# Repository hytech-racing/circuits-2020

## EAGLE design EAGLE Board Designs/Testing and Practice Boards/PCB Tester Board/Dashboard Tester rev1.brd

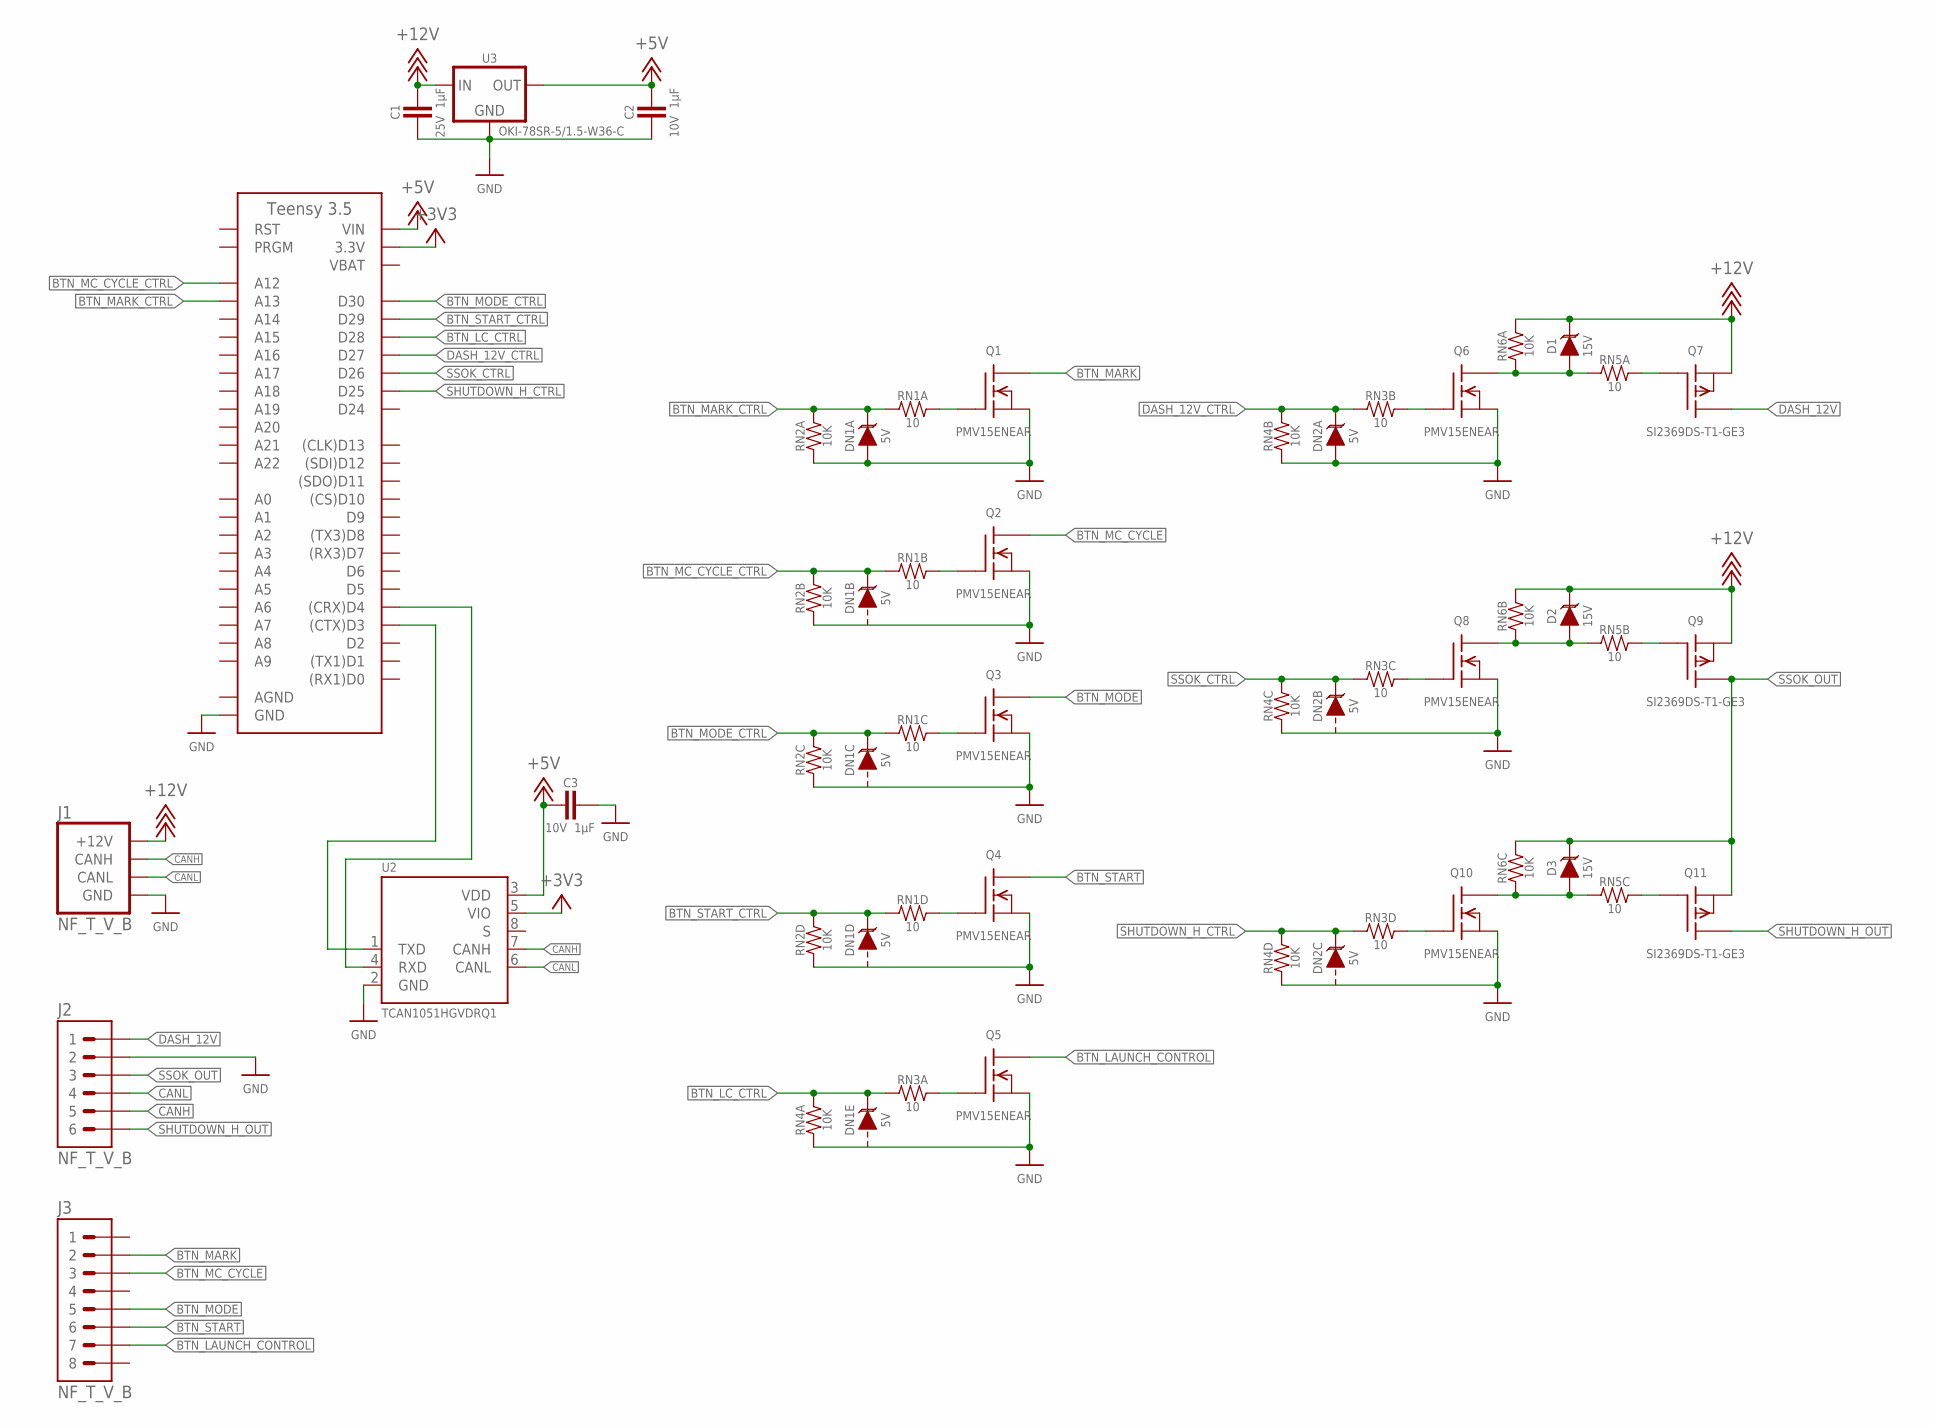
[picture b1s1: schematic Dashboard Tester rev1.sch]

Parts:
C1: CAPACITOR_0603_25V_1UF; 0603-CAP
C2, C3: CAPACITOR_0603_10V_1UF; 0603-CAP
D1, D2, D3: TVS_15V; SOT-23
DN1, DN2: TVS_ARRAY_5V; SOT363
J1: CONNECTOR-CAN_NF_T_V_BLACK; MOLEX_NANOFIT_PTH_04
J2: CONNECTOR-6_NF_T_V_BLACK; MOLEX_NANOFIT_PTH_06
J3: CONNECTOR-8_NF_T_V_BLACK; MOLEX_NANOFIT_PTH_08
Q1, Q2, Q3, Q4, Q5, Q6, Q8, Q10: TRANSISTOR_N_MOS_PMV15ENEA; SOT-23
Q7, Q9, Q11: TRANSISTOR_P_MOS_SOT23_SI2369DS-T1-GE3; SOT-23
RN1, RN3, RN5: RESISTOR_NETWORK_4_10; 1206-RES
RN2, RN4, RN6: RESISTOR_NETWORK_4_10K; 1206-RES
U1: TEENSY_3.5; TEENSY_LONG_EXT
U2: CAN_TRANSCIEVER_TCAN1051HQV-Q1; SOIC-08
U3: VOLTAGE_REGULATOR_OKI-78SR_5V; OKI-78SR

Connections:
+3V3: U1.3V3 (3.3V), U1.3V3@2 (3.3V), U1.3V3@3 (3.3V), U2.5 (VIO)
+5V: C2.1, C3.2, U1.VIN, U2.3 (VDD), U3.3 (OUT)
+12V: C1.1, D1.3 (C), D2.3 (C), J1.1 (+12V), Q7.2 (S), Q9.2 (S), RN6.7 (2), RN6.8 (2), U3.1 (IN)
AGND: U1.AGND/GND (AGND)
BTN_LAUNCH_CONTROL: J3.7, Q5.3 (D)
BTN_LC_CTRL: DN1.6 (C), RN3.1, RN4.8 (2), U1.D28
BTN_MARK: J3.2, Q1.3 (D)
BTN_MARK_CTRL: DN1.1 (C), RN1.1, RN2.8 (2), U1.D32 (A13)
BTN_MC_CYCLE: J3.3, Q2.3 (D)
BTN_MC_CYCLE_CTRL: DN1.3 (C), RN1.2 (1), RN2.7 (2), U1.D31 (A12)
BTN_MODE: J3.5, Q3.3 (D)
BTN_MODE_CTRL: DN1.4 (C), RN1.3 (1), RN2.6 (2), U1.D30
BTN_START: J3.6, Q4.3 (D)
BTN_START_CTRL: DN1.5 (C), RN1.4 (1), RN2.5 (2), U1.D29
CANH: J1.4 (CANH), J2.5, U2.7 (CANH)
CANL: J1.3 (CANL), J2.4, U2.6 (CANL)
DASH_12V: J2.1, Q7.3 (D)
DASH_12V_CTRL: DN2.1 (C), RN3.2 (1), RN4.7 (2), U1.D27
GND: C1.2, C2.2, C3.1, DN1.2 (A), DN2.2 (A), J1.2 (GND), J2.2, Q1.2 (S), Q2.2 (S), Q3.2 (S), Q4.2 (S), Q5.2 (S), Q6.2 (S), Q8.2 (S), Q10.2 (S), RN2.1, RN2.2 (1), RN2.3 (1), RN2.4 (1), RN4.1, RN4.2 (1), RN4.3 (1), RN4.4 (1), U1.GND, U1.GND@2 (GND), U1.GND@3 (GND), U2.2 (GND), U3.2 (GND)
unnamed: Q1.1 (G), RN1.8 (2)
unnamed: U1.D4 ((CRX)D4), U2.4 (RXD)
unnamed: Q6.1 (G), RN3.7 (2)
unnamed: Q2.1 (G), RN1.7 (2)
unnamed: Q3.1 (G), RN1.6 (2)
unnamed: Q4.1 (G), RN1.5 (2)
unnamed: Q5.1 (G), RN3.8 (2)
unnamed: Q8.1 (G), RN3.6 (2)
unnamed: Q9.1 (G), RN5.7 (2)
unnamed: D2.1 (A), Q8.3 (D), RN5.2 (1), RN6.2 (1)
unnamed: Q7.1 (G), RN5.8 (2)
unnamed: Q10.1 (G), RN3.5 (2)
unnamed: D1.1 (A), Q6.3 (D), RN5.1, RN6.1
unnamed: U1.D3 ((CTX)D3), U2.1 (TXD)
unnamed: Q11.1 (G), RN5.6 (2)
unnamed: D3.1 (A), Q10.3 (D), RN5.3 (1), RN6.3 (1)
SHUTDOWN_H_CTRL: DN2.4 (C), RN3.4 (1), RN4.5 (2), U1.D25
SHUTDOWN_H_OUT: J2.6, Q11.3 (D)
SSOK_CTRL: DN2.3 (C), RN3.3 (1), RN4.6 (2), U1.D26
SSOK_OUT: D3.3 (C), J2.3, Q9.3 (D), Q11.2 (S), RN6.6 (2)
VBAT: U1.VBAT

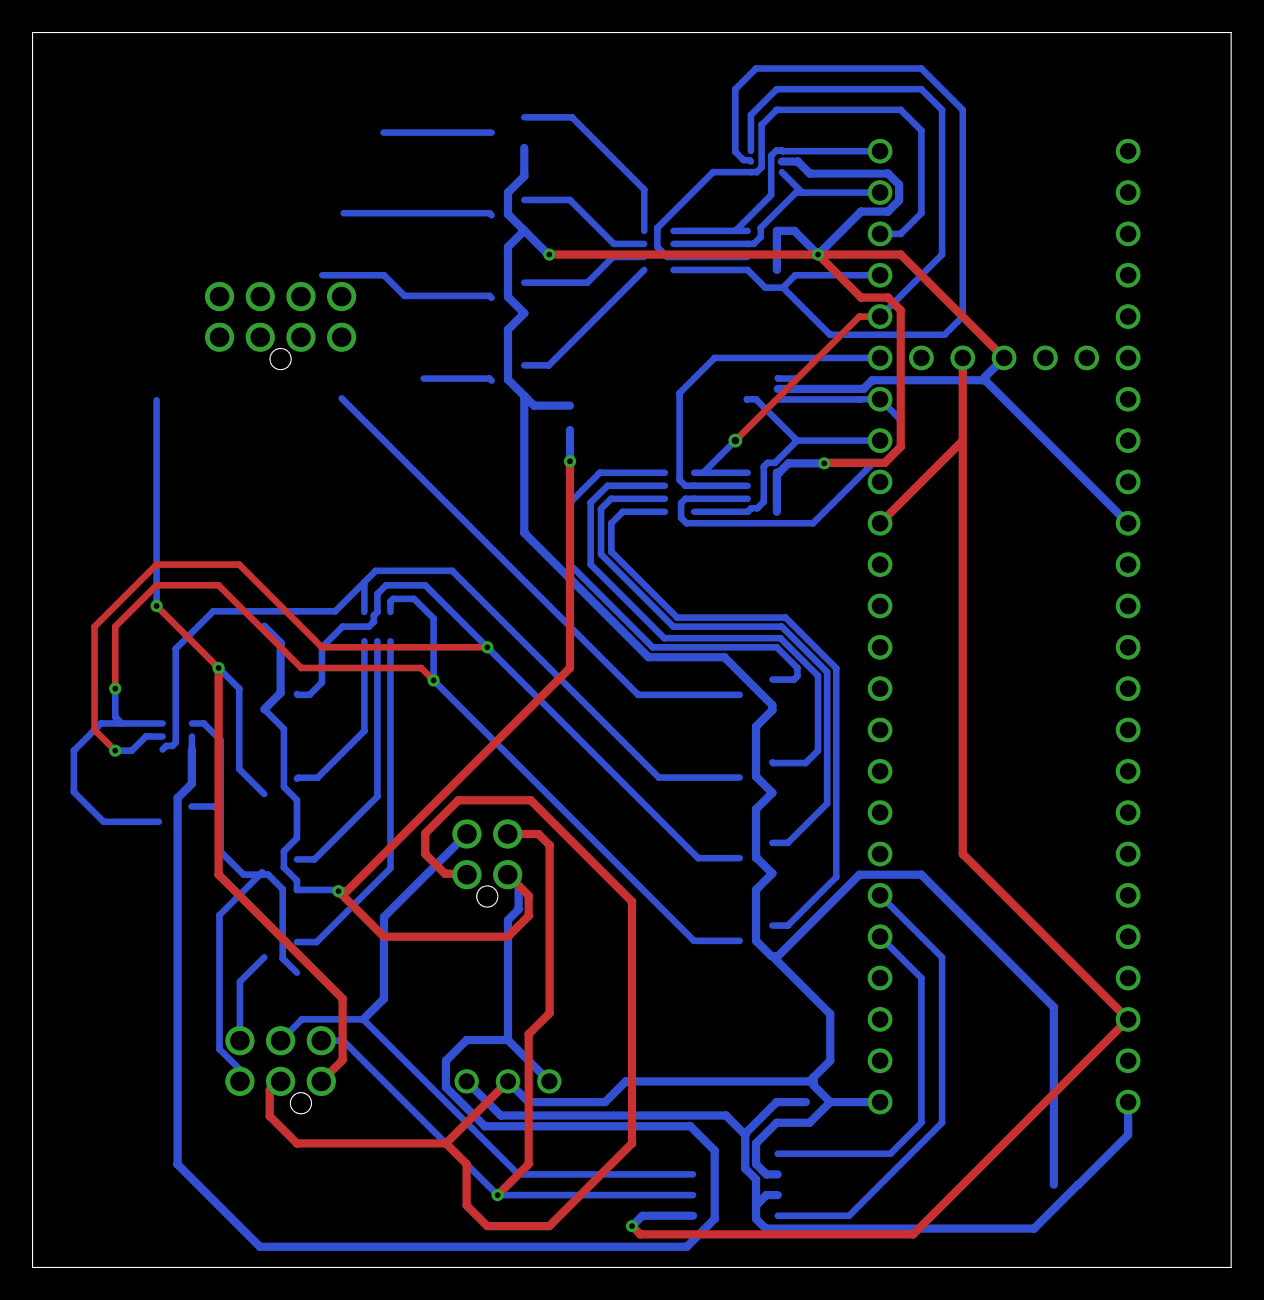
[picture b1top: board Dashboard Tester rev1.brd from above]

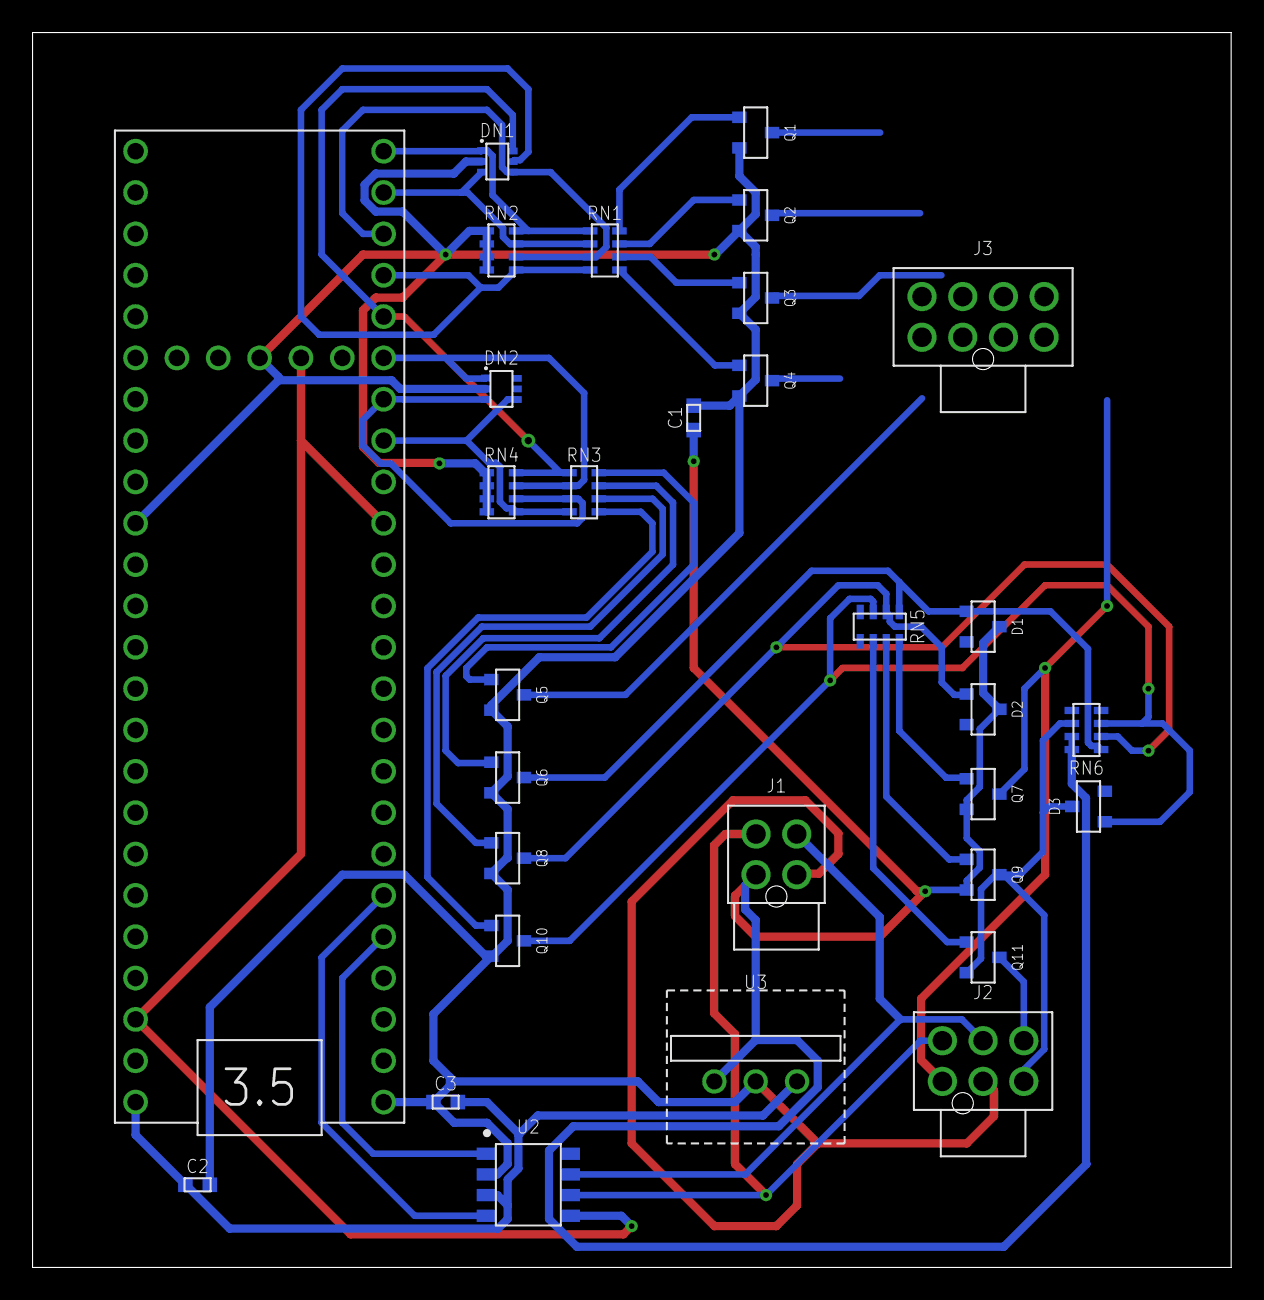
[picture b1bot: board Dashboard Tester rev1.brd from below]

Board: 2 copper layers, 73.6 x 75.9 mm, 31 parts (31 on the bottom side), 38 nets.

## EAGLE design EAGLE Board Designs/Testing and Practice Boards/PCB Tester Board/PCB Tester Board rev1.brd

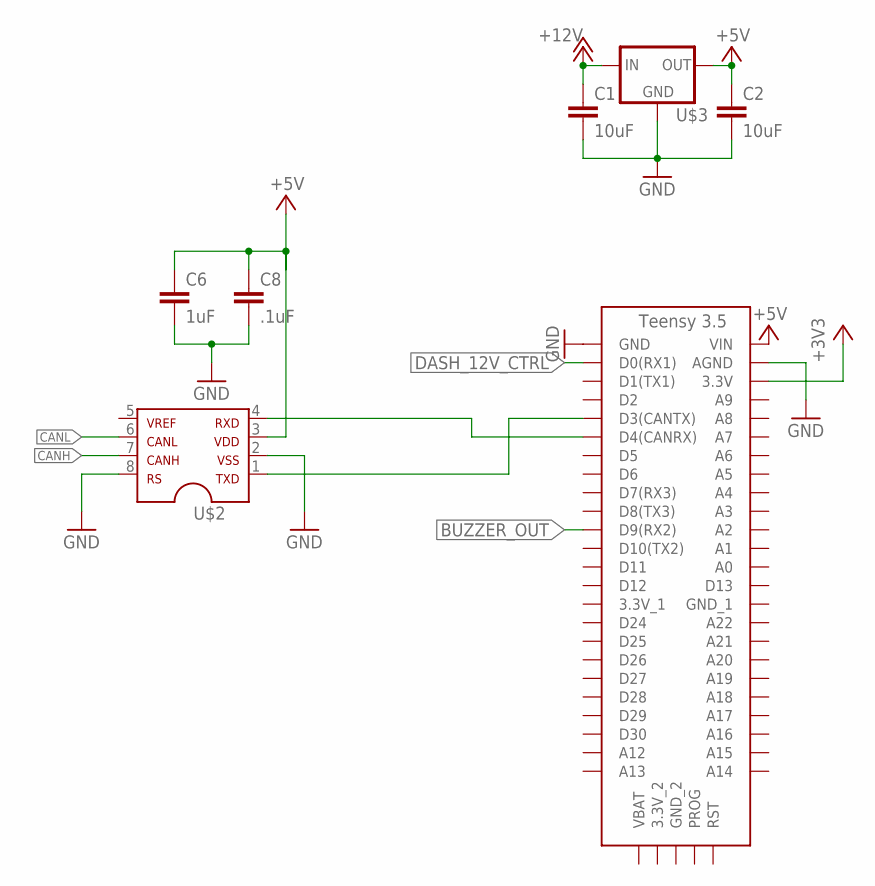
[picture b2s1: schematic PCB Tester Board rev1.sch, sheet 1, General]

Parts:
C1, C2: 10uF; 0603-CAP
C6: 1uF; 0603-CAP
C8: .1uF; 0603-CAP
U$2: MCP2551; SOIC-08
U$3: OKI-78SR-5; OKI-78SR
U$10: TEENSY_3.5_EXT

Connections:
+3V3: U$10.3.3V; also elsewhere on the board
+5V: C2.1, C6.1, C8.1, U$2.3, U$3.3 (OUT), U$10.VIN; also elsewhere on the board
+12V: C1.1, U$3.1 (IN); also elsewhere on the board
BUZZER_OUT: U$10.D9(RX2); also elsewhere on the board
CANH: U$2.7; also elsewhere on the board
CANL: U$2.6; also elsewhere on the board
DASH_12V_CTRL: U$10.D0(RX1); also elsewhere on the board
GND: C1.2, C2.2, C6.2, C8.2, U$2.2, U$2.8, U$3.2 (GND), U$10.AGND, U$10.GND; also elsewhere on the board
unnamed: U$2.1, U$10.D3(CANTX)
unnamed: U$2.4, U$10.D4(CANRX)

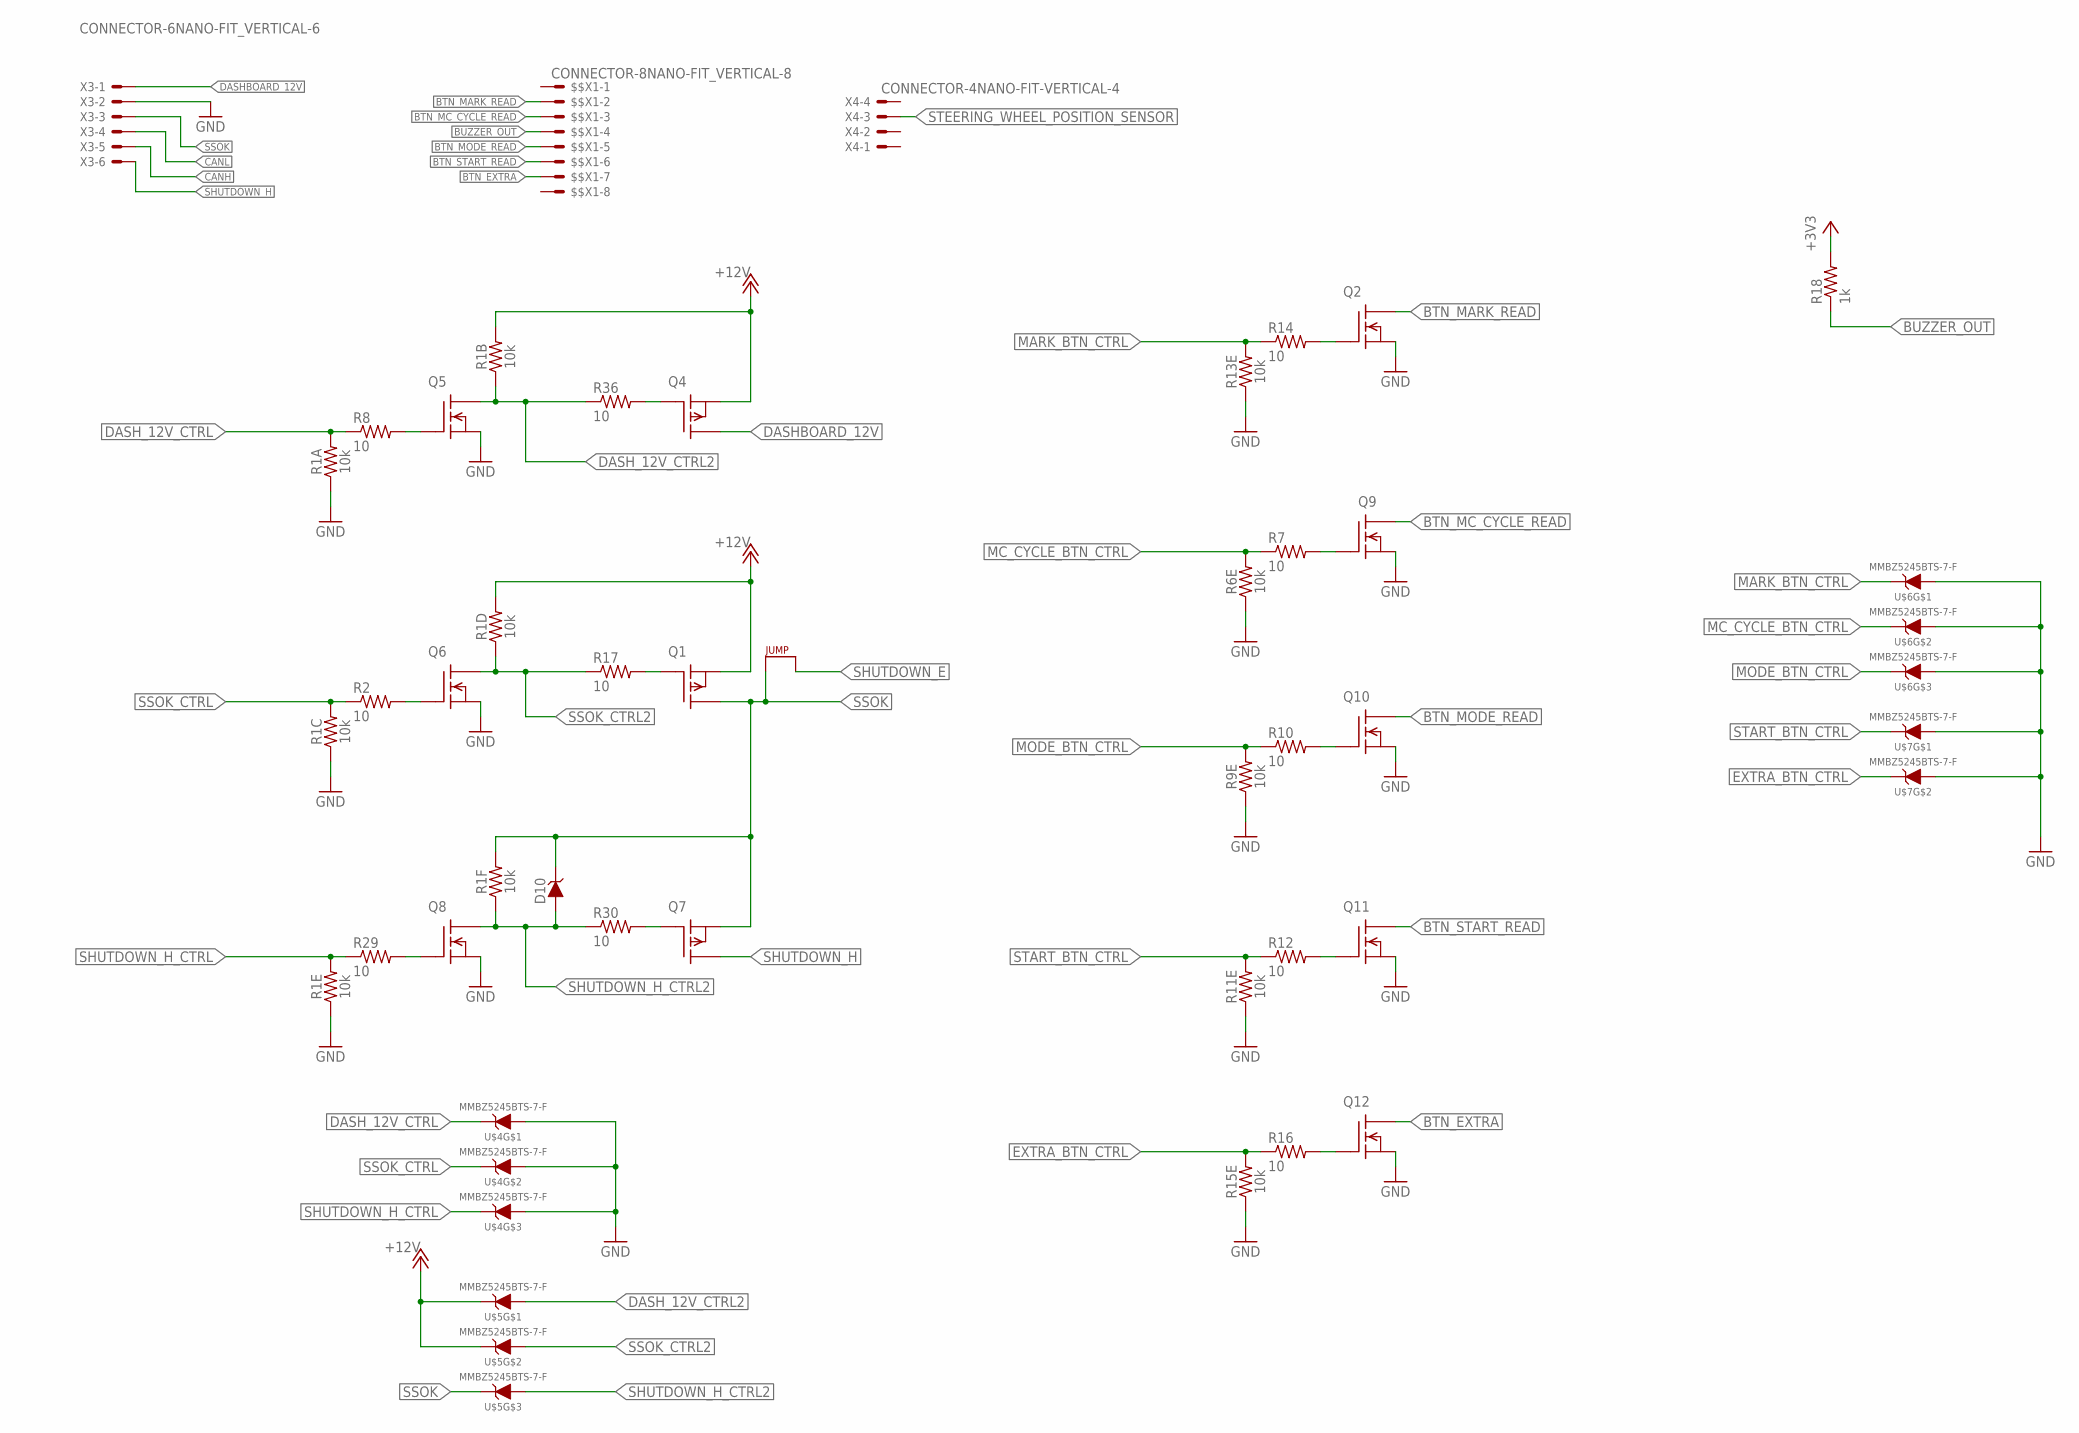
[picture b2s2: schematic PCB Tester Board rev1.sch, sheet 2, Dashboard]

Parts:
$$X1: CONNECTOR-8NANO-FIT_VERTICAL-8; NANO-FIT_VERTICAL-8
D10: DIODE_ZENER; SOT23
J4: JUMPER.1; 1X02
Q1, Q4, Q7: P-CHANNEL_MOSFET_DMP3099L-7; SOT23
Q2, Q5, Q6, Q8, Q9, Q10, Q11, Q12: DMG3406LSOT; SOT23
R1, R6, R9, R11, R13, R15: 10k; YAG_YC248-M
R2, R7, R8, R10, R12, R14, R16, R17, R29, R30, R36: 10; 0603-RES
R18: 1k; 0603-RES
U$4, U$5, U$6, U$7: MMBZ5245BTS-7-F; SOT363
X3: CONNECTOR-6NANO-FIT_VERTICAL-6; NANO-FIT_VERTICAL-6
X4: CONNECTOR-4NANO-FIT-VERTICAL-4; NANO-FIT_VERTICAL-4

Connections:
+3V3: R18.2; also elsewhere on the board
+12V: Q1.2 (S), Q4.2 (S), R1.13 (2), R1.15 (2), U$5.P$4 (C), U$5.P$5 (C); also elsewhere on the board
BTN_EXTRA: $$X1.P$7, Q12.3 (D)
BTN_MARK_READ: $$X1.P$2, Q2.3 (D)
BTN_MC_CYCLE_READ: $$X1.P$3, Q9.3 (D)
BTN_MODE_READ: $$X1.P$5, Q10.3 (D)
BTN_START_READ: $$X1.P$6, Q11.3 (D)
BUZZER_OUT: $$X1.P$4, R18.1; also elsewhere on the board
CANH: X3.P$5; also elsewhere on the board
CANL: X3.P$4; also elsewhere on the board
DASHBOARD_12V: Q4.3 (D), X3.P$1
DASH_12V_CTRL: R1.16 (2), R8.1, U$4.P$4 (C); also elsewhere on the board
DASH_12V_CTRL2: Q5.3 (D), R1.2 (1), R36.1, U$5.P$1 (A)
EXTRA_BTN_CTRL: R15.12 (2), R16.1, U$7.P$5 (C)
GND: Q2.2 (S), Q5.2 (S), Q6.2 (S), Q8.2 (S), Q9.2 (S), Q10.2 (S), Q11.2 (S), Q12.2 (S), R1.1, R1.3 (1), R1.5 (1), R6.5 (1), R9.5 (1), R11.5 (1), R13.5 (1), R15.5 (1), U$4.P$1 (A), U$4.P$2 (A), U$4.P$3 (A), U$6.P$1 (A), U$6.P$2 (A), U$6.P$3 (A), U$7.P$1 (A), U$7.P$2 (A), X3.P$2; also elsewhere on the board
MARK_BTN_CTRL: R13.12 (2), R14.1, U$6.P$4 (C)
MC_CYCLE_BTN_CTRL: R6.12 (2), R7.1, U$6.P$5 (C)
MODE_BTN_CTRL: R9.12 (2), R10.1, U$6.P$6 (C)
unnamed: Q9.1 (G), R7.2
unnamed: Q10.1 (G), R10.2
unnamed: Q11.1 (G), R12.2
unnamed: Q5.1 (G), R8.2
unnamed: Q12.1 (G), R16.2
unnamed: Q2.1 (G), R14.2
unnamed: Q6.1 (G), R2.2
unnamed: Q1.1 (G), R17.2
unnamed: Q8.1 (G), R29.2
unnamed: Q7.1 (G), R30.2
unnamed: Q4.1 (G), R36.2
SHUTDOWN_E: J4.2; also elsewhere on the board
SHUTDOWN_H: Q7.3 (D), X3.P$6
SHUTDOWN_H_CTRL: R1.12 (2), R29.1, U$4.P$6 (C)
SHUTDOWN_H_CTRL2: D10.1 (A), Q8.3 (D), R1.6 (1), R30.1, U$5.P$3 (A)
SSOK: D10.3 (C), J4.1, Q1.3 (D), Q7.2 (S), R1.11 (2), U$5.P$6 (C), X3.P$3
SSOK_CTRL: R1.14 (2), R2.1, U$4.P$5 (C)
SSOK_CTRL2: Q6.3 (D), R1.4 (1), R17.1, U$5.P$2 (A)
START_BTN_CTRL: R11.12 (2), R12.1, U$7.P$4 (C)
STEERING_WHEEL_POSITION_SENSOR: X4.P$3

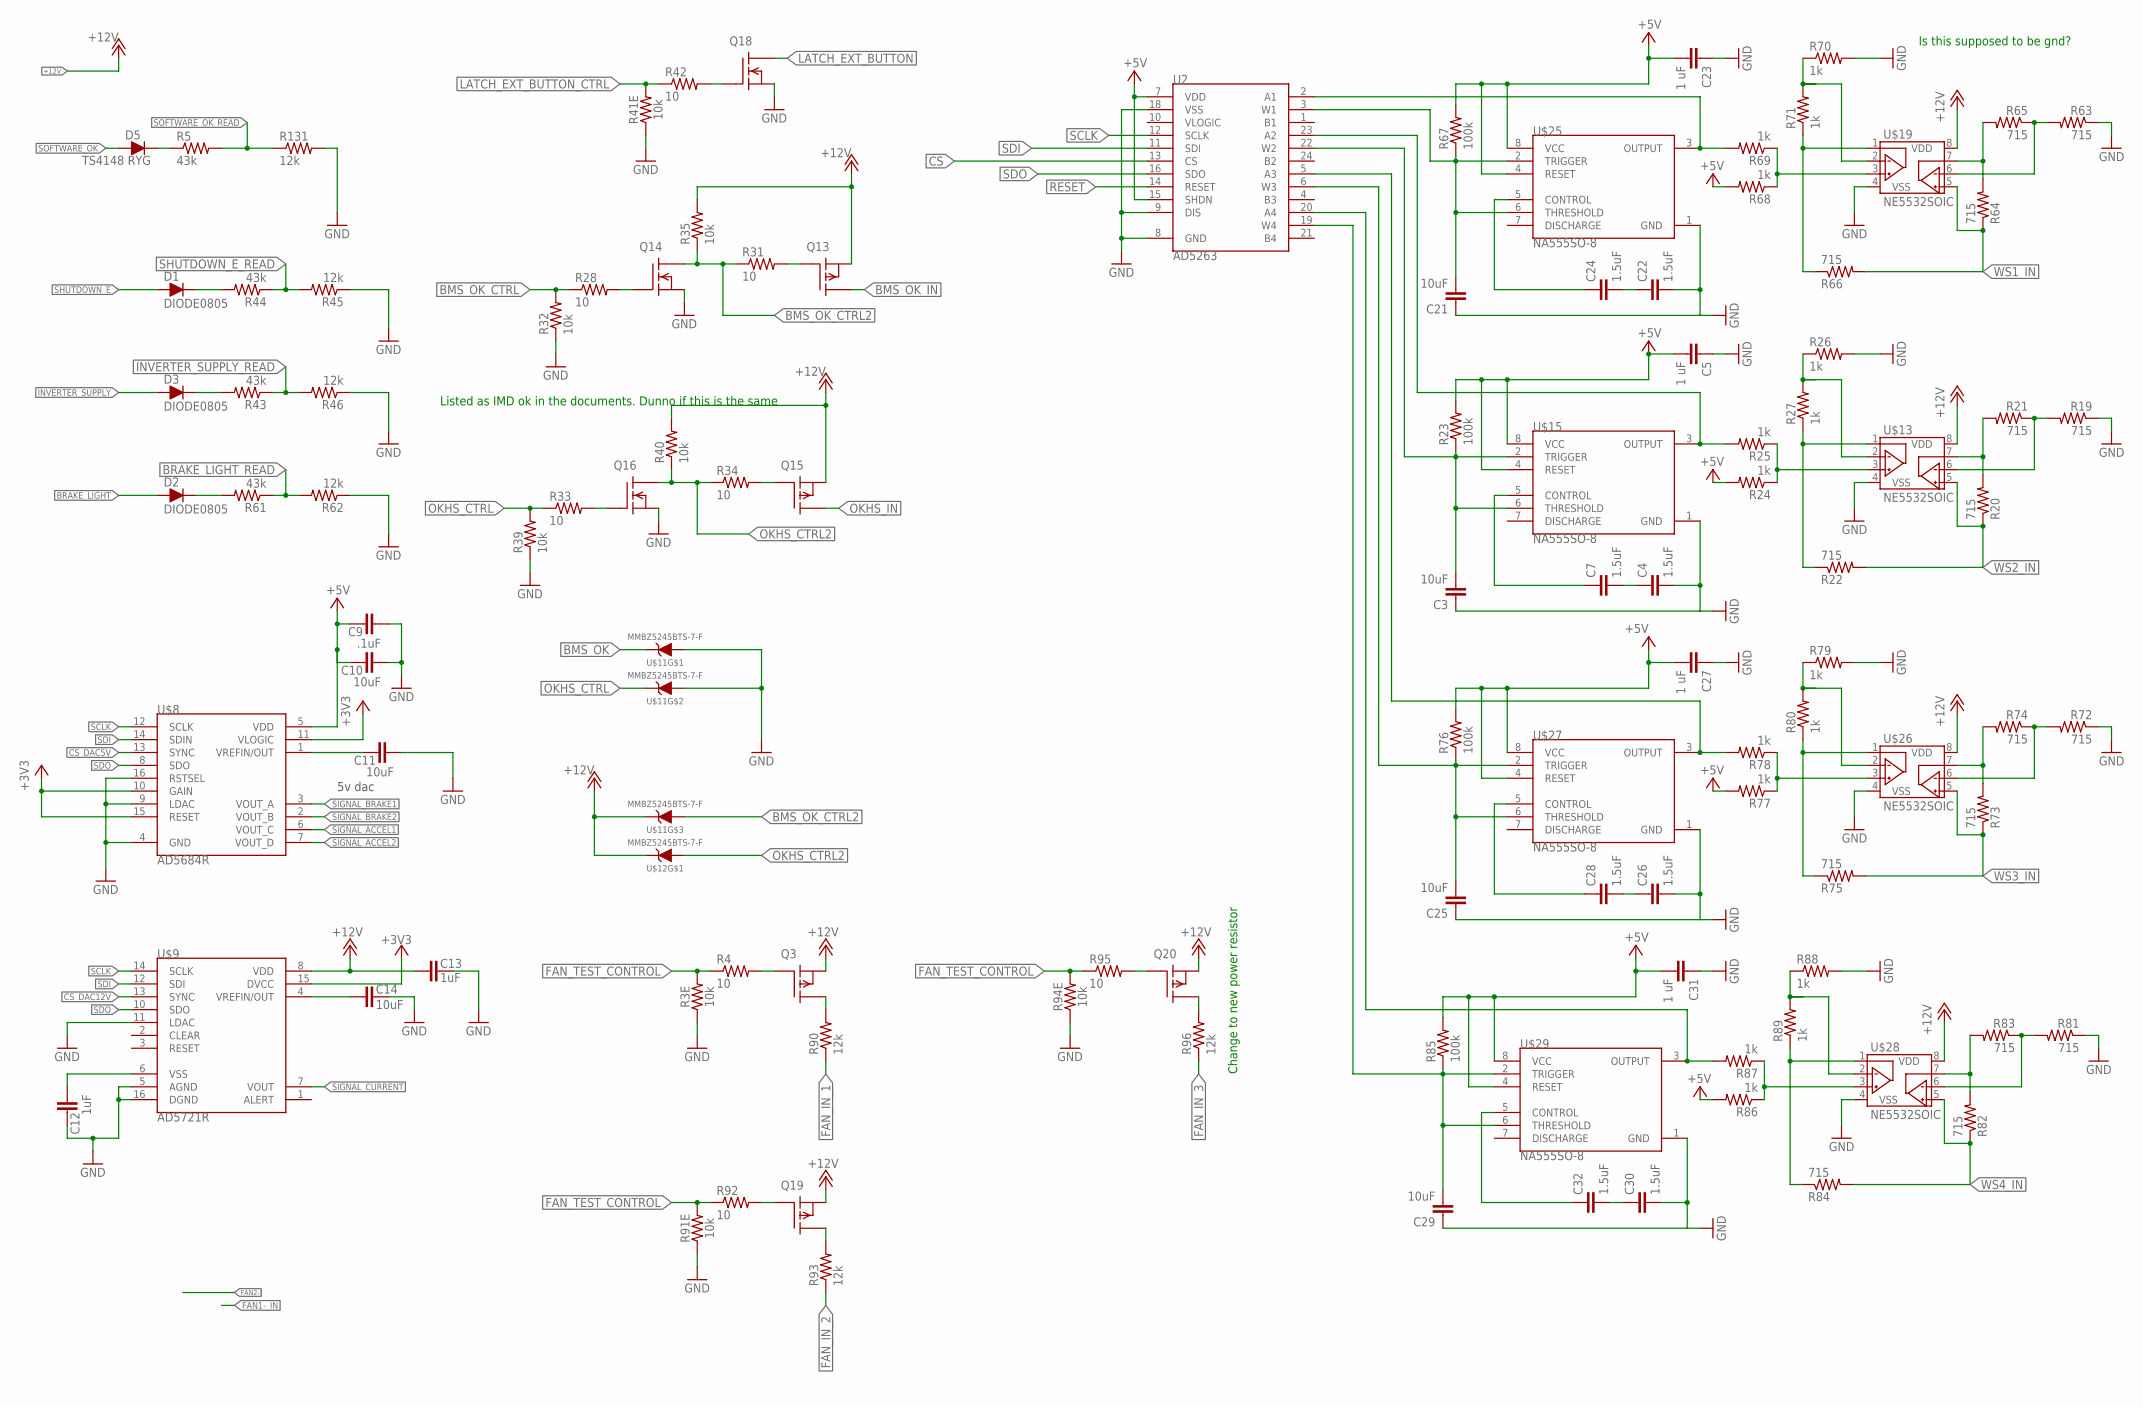
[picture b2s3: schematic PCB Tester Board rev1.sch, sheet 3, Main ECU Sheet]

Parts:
C3, C10, C11, C14, C21, C25, C29: 10uF; 0603-CAP
C4, C7, C22, C24, C26, C28, C30, C32: 1.5uF; 0603-CAP
C5, C23, C27, C31: 1 uF; 0603-CAP
C9: .1uF; 0603-CAP
C12, C13: 1uF; 0603-CAP
D1, D2, D3: DIODE0805; 0805_D
D5: TS4148 RYG; 0805_D
Q3, Q13, Q15, Q19, Q20: P-CHANNEL_MOSFET_DMP3099L-7; SOT23
Q14, Q16, Q18: DMG3406LSOT; SOT23
R3, R41, R91, R94: 10k; YAG_YC248-M
R4, R28, R31, R33, R34, R42, R92, R95: 10; 0603-RES
R5, R43, R44, R61: 43k; 0603-RES
R19, R20, R21, R22, R63, R64, R65, R66, R72, R73, R74, R75, R81, R82, R83, R84: 715; 0603-RES
R23, R67, R76, R85: 100k; 0603-RES
R24, R25, R26, R27, R68, R69, R70, R71, R77, R78, R79, R80, R86, R87, R88, R89: 1k; 0603-RES
R32, R35, R39, R40: 10k; 0603-RES
R45, R46, R62, R131: 12k; 0603-RES
R90, R93, R96: 12k; 10W_RESISTOR_VISHAY
U2: AD5263; TSSOP-24
U$8: AD5684R; TSSOP-16
U$9: AD5721R; TSSOP-16
U$11, U$12: MMBZ5245BTS-7-F; SOT363
U$13, U$19, U$26, U$28: NE5532SOIC; SOIC-08
U$15, U$25, U$27, U$29: NA555SO-8; SOIC-08

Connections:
555_GND: C3.1, C4.2, C21.1, C22.2, C25.1, C26.2, C29.1, C30.2, U$15.1 (GND), U$25.1 (GND), U$27.1 (GND), U$29.1 (GND)
+3V3: U$8.10 (GAIN), U$8.11 (VLOGIC), U$8.15 (RESET), U$9.15 (DVCC); also elsewhere on the board
+5V: C5.2, C9.1, C10.1, C23.2, C27.2, C31.2, R23.2, R24.2, R67.2, R68.2, R76.2, R77.2, R85.2, R86.2, U2.7 (VDD), U2.15 (SHDN), U$8.5 (VDD), U$15.4 (RESET), U$15.8 (VCC), U$25.4 (RESET), U$25.8 (VCC), U$27.4 (RESET), U$27.8 (VCC), U$29.4 (RESET), U$29.8 (VCC); also elsewhere on the board
+12V: C13.2, Q3.2 (S), Q13.2 (S), Q15.2 (S), Q19.2 (S), Q20.2 (S), R35.2, R40.2, U$9.8 (VDD), U$11.P$6 (C), U$12.P$4 (C), U$13.8 (VDD), U$19.8 (VDD), U$26.8 (VDD), U$28.8 (VDD); also elsewhere on the board
ALTERNATINGVOLTAGE1: R66.1, R71.1, U$19.1 (VOUTA)
ALTERNATINGVOLTAGE2: R22.1, R27.1, U$13.1 (VOUTA)
ALTERNATINGVOLTAGE3: R75.1, R80.1, U$26.1 (VOUTA)
ALTERNATINGVOLTAGE4: R84.1, R89.1, U$28.1 (VOUTA)
BMS_OK: U$11.P$4 (C)
BMS_OK_CTRL: R28.1, R32.2
BMS_OK_CTRL2: Q14.3 (D), R31.1, R35.1, U$11.P$3 (A)
BMS_OK_IN: Q13.3 (D)
BRAKE_LIGHT: D2.A
BRAKE_LIGHT_READ: R61.1, R62.2
CS: U2.13 (CS)
CS_DAC5V: U$8.13 (SYNC); also elsewhere on the board
CS_DAC12V: U$9.13 (SYNC); also elsewhere on the board
FAN_IN_1: R90.1
FAN_IN_2: R93.1
FAN_IN_3: R96.1
FAN_TEST_CONTROL: R3.12 (2), R4.1, R91.12 (2), R92.1, R94.12 (2), R95.1
GND: C5.1, C9.2, C10.2, C11.2, C12.1, C13.1, C14.1, C23.1, C27.1, C31.1, Q14.2 (S), Q16.2 (S), Q18.2 (S), R3.5 (1), R19.1, R26.2, R32.1, R39.1, R41.5 (1), R45.1, R46.1, R62.1, R63.1, R70.2, R72.1, R79.2, R81.1, R88.2, R91.5 (1), R94.5 (1), R131.2, U2.8 (GND), U2.9 (DIS), U2.18 (VSS), U$8.4 (GND), U$8.9 (LDAC), U$8.16 (RSTSEL), U$9.5 (AGND), U$9.11 (LDAC), U$9.16 (DGND), U$11.P$1 (A), U$11.P$2 (A), U$13.4 (VSS), U$19.4 (VSS), U$26.4 (VSS), U$28.4 (VSS); also elsewhere on the board
INVERTER_SUPPLY: D3.A
INVERTER_SUPPLY_READ: R43.1, R46.2
LATCH_EXT_BUTTON: Q18.3 (D)
LATCH_EXT_BUTTON_CTRL: R41.12 (2), R42.1
unnamed: Q3.1 (G), R4.2
unnamed: C11.1, U$8.1 (VREFIN/OUT)
unnamed: D5.C, R5.1
unnamed: Q14.1 (G), R28.2
unnamed: Q13.1 (G), R31.2
unnamed: Q16.1 (G), R33.2
unnamed: Q15.1 (G), R34.2
unnamed: C12.2, U$9.6 (VSS)
unnamed: R69.2, U2.2 (A1), U$25.3 (OUTPUT)
unnamed: R25.2, U2.23 (A2), U$15.3 (OUTPUT)
unnamed: R24.1, R25.1, U$13.3 (VINA+)
unnamed: R20.2, R21.2, U$13.7 (VOUTB)
unnamed: R26.1, R27.2, U$13.2 (VINA-)
unnamed: C3.2, R23.1, U2.22 (W2), U$15.2 (TRIGGER), U$15.6 (THRESHOLD)
unnamed: C7.1, U$15.5 (CONTROL)
unnamed: C14.2, U$9.4 (VREFIN/OUT)
unnamed: C4.1, C7.2
unnamed: R19.2, R21.1, U$13.6 (VINB-)
unnamed: D3.C, R43.2
unnamed: D1.C, R44.2
unnamed: D2.C, R61.2
unnamed: Q18.1 (G), R42.2
unnamed: R68.1, R69.1, U$19.3 (VINA+)
unnamed: R64.2, R65.2, U$19.7 (VOUTB)
unnamed: R70.1, R71.2, U$19.2 (VINA-)
unnamed: C21.2, R67.1, U2.3 (W1), U$25.2 (TRIGGER), U$25.6 (THRESHOLD)
unnamed: C24.1, U$25.5 (CONTROL)
unnamed: C22.1, C24.2
unnamed: R63.2, R65.1, U$19.6 (VINB-)
unnamed: R78.2, U2.5 (A3), U$27.3 (OUTPUT)
unnamed: R77.1, R78.1, U$26.3 (VINA+)
unnamed: R73.2, R74.2, U$26.7 (VOUTB)
unnamed: R79.1, R80.2, U$26.2 (VINA-)
unnamed: Q3.3 (D), R90.2
unnamed: C28.1, U$27.5 (CONTROL)
unnamed: C26.1, C28.2
unnamed: R72.2, R74.1, U$26.6 (VINB-)
unnamed: R87.2, U2.20 (A4), U$29.3 (OUTPUT)
unnamed: R86.1, R87.1, U$28.3 (VINA+)
unnamed: R82.2, R83.2, U$28.7 (VOUTB)
unnamed: R88.1, R89.2, U$28.2 (VINA-)
unnamed: C29.2, R85.1, U2.19 (W4), U$29.2 (TRIGGER), U$29.6 (THRESHOLD)
unnamed: C32.1, U$29.5 (CONTROL)
unnamed: C30.1, C32.2
unnamed: R81.2, R83.1, U$28.6 (VINB-)
unnamed: Q19.1 (G), R92.2
unnamed: Q19.3 (D), R93.2
unnamed: Q20.1 (G), R95.2
unnamed: Q20.3 (D), R96.2
unnamed: C25.2, R76.1, U2.6 (W3), U$27.2 (TRIGGER), U$27.6 (THRESHOLD)
OKHS_CTRL: R33.1, R39.2, U$11.P$5 (C)
OKHS_CTRL2: Q16.3 (D), R34.1, R40.1, U$12.P$1 (A)
OKHS_IN: Q15.3 (D)
RESET: U2.14 (RESET)
SCLK: U2.12 (SCLK), U$8.12 (SCLK), U$9.14 (SCLK); also elsewhere on the board
SDI: U2.11 (SDI), U$8.14 (SDIN), U$9.12 (SDI); also elsewhere on the board
SDO: U2.16 (SDO), U$8.8 (SDO), U$9.10 (SDO); also elsewhere on the board
SHUTDOWN_E: D1.A; also elsewhere on the board
SHUTDOWN_E_READ: R44.1, R45.2
SIGNAL_ACCEL1: U$8.6 (VOUT_C)
SIGNAL_ACCEL2: U$8.7 (VOUT_D)
SIGNAL_BRAKE1: U$8.3 (VOUT_A)
SIGNAL_BRAKE2: U$8.2 (VOUT_B)
SIGNAL_CURRENT: U$9.7 (VOUT)
SOFTWARE_OK: D5.A
SOFTWARE_OK_READ: R5.2, R131.1
WS1_IN: R64.1, R66.2, U$19.5 (VINB+)
WS2_IN: R20.1, R22.2, U$13.5 (VINB+)
WS3_IN: R73.1, R75.2, U$26.5 (VINB+)
WS4_IN: R82.1, R84.2, U$28.5 (VINB+)

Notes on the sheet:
5v dac
Listed as IMD ok in the documents. Dunno if this is the same
Is this supposed to be gnd?
Change to new power resistor
